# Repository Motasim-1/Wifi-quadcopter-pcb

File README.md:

# WiFi-Controlled Quadcopter PCB Using ESP32

Custom PCB design for a WiFi-controlled quadcopter based on the ESP32 microcontroller. The board was designed in KiCad, assembled using solder paste and a reflow oven, and tested with four motor outputs controlled through a mobile app.

## Project overview

The goal of this project was to design a compact quadcopter control PCB that integrates the main electronics on a single board and reduces external wiring.

## Key features

- ESP32-based control board with built-in WiFi capability
- Custom quadcopter-shaped PCB designed in KiCad
- Four motor-control outputs using MOSFET driver stages
- USB interface for programming/debugging
- SMD assembly using solder paste and reflow oven
- Power verification and short-circuit testing after assembly
- Functional motor testing using mobile-app WiFi control

## Hardware design

The KiCad project is located in:

```text
hardware/kicad/
```

Included schematic sheets:

```text
my_drone.kicad_sch
mcu.kicad_sch
motor.kicad_sch
power.kicad_sch
usb.kicad_sch
imu.kicad_sch
```

The PCB layout file is:

```text
my_drone.kicad_pcb
```

## Figures

### KiCad 3D view

### Assembled PCB

### Motor test setup

## Tools and technologies

- KiCad
- ESP32
- PCB design
- SMD soldering
- Reflow soldering
- MOSFET motor switching
- WiFi-based control
- Hardware testing and troubleshooting

## Firmware note

The original motor-control setup was tested using an existing mobile-control framework. This repository focuses on the custom PCB hardware design, assembly and validation. 
## Repository structure

```text
wifi-controlled-quadcopter-pcb/
├── README.md
├── .gitignore
├── hardware/
│   └── kicad/
├── figures/
## Documentation

- [View complete schematic (PDF)](docs/quadcopter_schematic.pdf)

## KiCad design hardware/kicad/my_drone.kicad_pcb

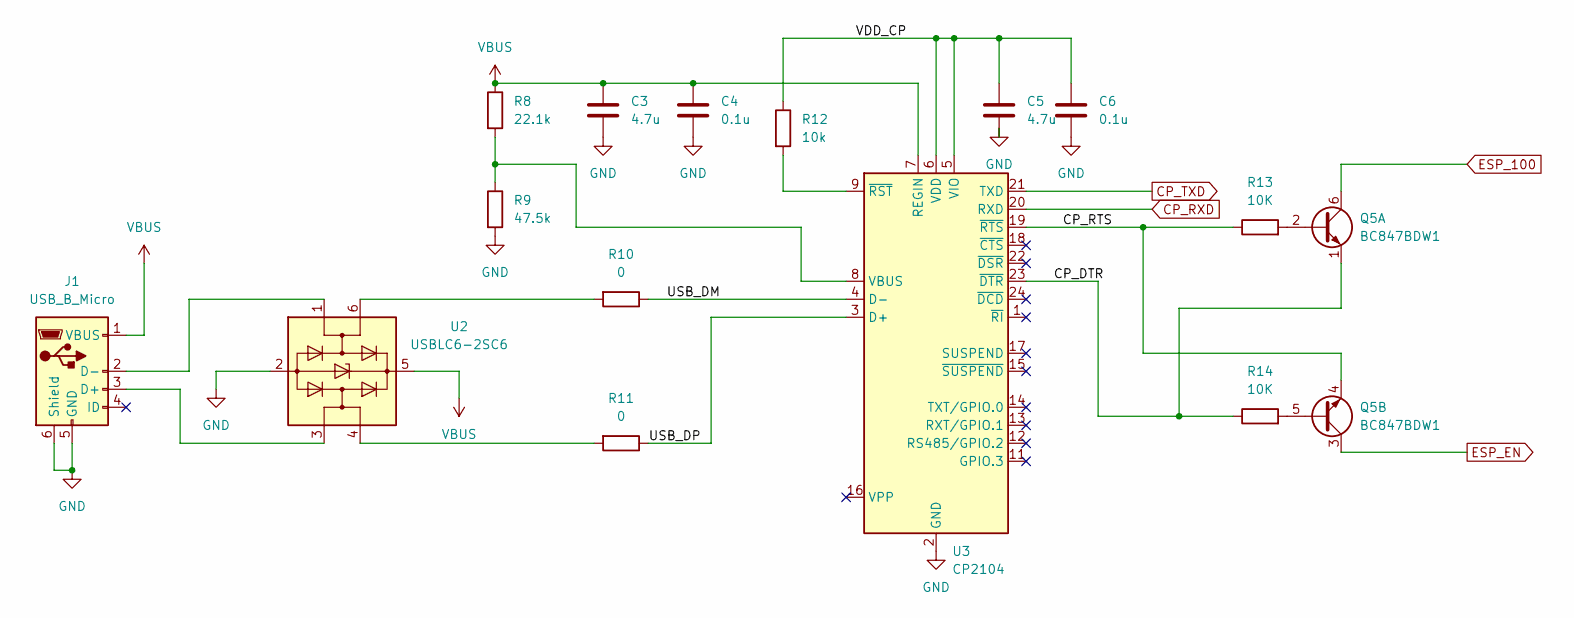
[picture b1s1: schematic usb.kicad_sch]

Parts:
C3, C5: 4.7u; C_0603_1608Metric
C4, C6: 0.1u; C_0603_1608Metric
J1: USB_B_Micro; USB_Micro
Q5: BC847BDW1; SOT-363_SC-70-6
R8: 22.1k; R_0603_1608Metric
R9: 47.5k; R_0603_1608Metric
R10, R11: 0; R_0603_1608Metric
R12: 10k; R_0603_1608Metric
R13, R14: 10K; R_0603_1608Metric
U2: USBLC6-2SC6; SOT-23-6; Digi-Key 497-5235-1-ND
U3: CP2104; QFN-24-1EP_4x4mm_P0.5mm_EP2.6x2.6mm; Digi-Key 336-4146-1-ND

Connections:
/*USB/CP_DTR: Q5.1 (E1), R14.1, U3.23 (~DTR)
/*USB/CP_RTS: Q5.4 (E2), R13.1, U3.19 (~RTS)
/*USB/USB_DM: R10.1, U3.4 (D-)
/*USB/USB_DP: R11.1, U3.3 (D+)
/*USB/VDD_CP: C5.1, C6.1, R12.1, U3.5 (VIO), U3.6 (VDD)
CP_RXD: U3.20 (RXD); also elsewhere on the board
CP_TXD: U3.21 (TXD); also elsewhere on the board
ESP_100: Q5.6 (C1); also elsewhere on the board
ESP_EN: Q5.3 (C2); also elsewhere on the board
GND: C3.2, C4.2, C5.2, C6.2, J1.5 (GND), J1.6 (Shield), R9.2, U2.2 (GND), U3.2 (GND), U3.25 (GND); also elsewhere on the board
unnamed: J1.3 (D+), U2.3 (I/O2)
unnamed: J1.2 (D-), U2.1 (I/O1)
unnamed: Q5.2 (B1), R13.2
unnamed: Q5.5 (B2), R14.2
unnamed: R10.2, U2.6 (I/O1)
unnamed: R11.2, U2.4 (I/O2)
unnamed: R8.2, R9.1, U3.8 (VBUS)
unnamed: R12.2, U3.9 (~RST)
VBUS: C3.1, C4.1, J1.1 (VBUS), R8.1, U2.5 (VBUS), U3.7 (REGIN); also elsewhere on the board

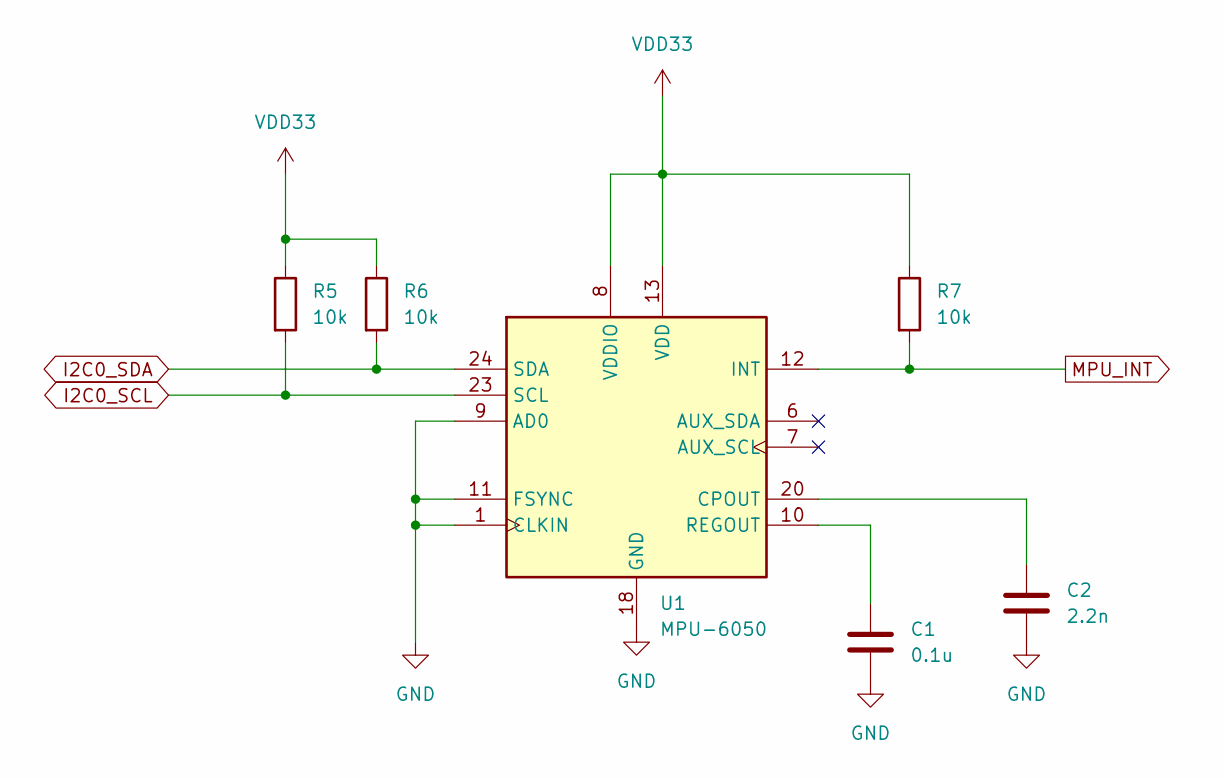
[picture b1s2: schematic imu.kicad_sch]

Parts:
C1: 0.1u; C_0603_1608Metric
C2: 2.2n; C_0603_1608Metric
R5, R6, R7: 10k; R_0603_1608Metric
U1: MPU-6050; InvenSense_QFN-24_4x4mm_P0.5mm

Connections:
GND: C1.2, C2.2, U1.1 (CLKIN), U1.9 (AD0), U1.11 (FSYNC), U1.18 (GND); also elsewhere on the board
I2C0_SCL: R5.2, U1.23 (SCL); also elsewhere on the board
I2C0_SDA: R6.2, U1.24 (SDA); also elsewhere on the board
MPU_INT: R7.2, U1.12 (INT); also elsewhere on the board
unnamed: C2.1, U1.20 (CPOUT)
unnamed: C1.1, U1.10 (REGOUT)
VDD33: R5.1, R6.1, R7.1, U1.8 (VDDIO), U1.13 (VDD); also elsewhere on the board

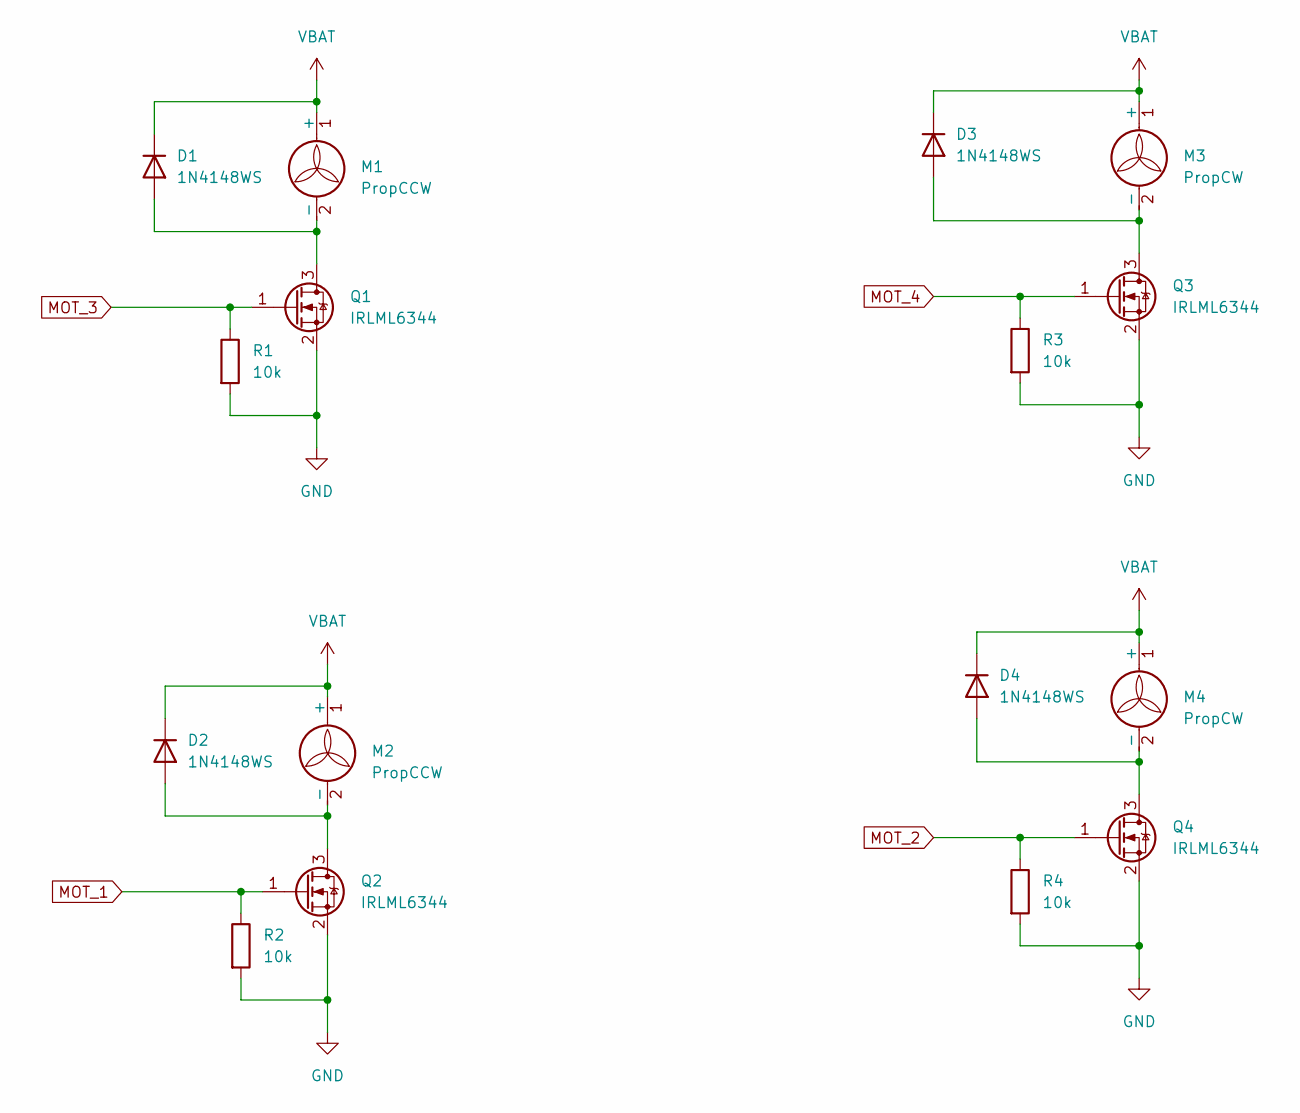
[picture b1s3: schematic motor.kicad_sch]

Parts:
D1, D2, D3, D4: 1N4148WS; D_SOD-323
M1, M2: PropCCW; PinHeader_1x02_P2.54mm_Vertical
M3, M4: PropCW; PinHeader_1x02_P2.54mm_Vertical
Q1, Q2, Q3, Q4: IRLML6344; SOT-23; Digi-Key IRLML6344TRPBFCT-ND
R1, R2, R3, R4: 10k; R_0603_1608Metric

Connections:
GND: Q1.2 (S), Q2.2 (S), Q3.2 (S), Q4.2 (S), R1.2, R2.2, R3.2, R4.2; also elsewhere on the board
MOT_1: Q2.1 (G), R2.1; also elsewhere on the board
MOT_2: Q4.1 (G), R4.1; also elsewhere on the board
MOT_3: Q1.1 (G), R1.1; also elsewhere on the board
MOT_4: Q3.1 (G), R3.1; also elsewhere on the board
unnamed: D1.2 (A), M1.2 (-), Q1.3 (D)
unnamed: D2.2 (A), M2.2 (-), Q2.3 (D)
unnamed: D3.2 (A), M3.2 (-), Q3.3 (D)
unnamed: D4.2 (A), M4.2 (-), Q4.3 (D)
VBAT: D1.1 (K), D2.1 (K), D3.1 (K), D4.1 (K), M1.1 (+), M2.1 (+), M3.1 (+), M4.1 (+); also elsewhere on the board

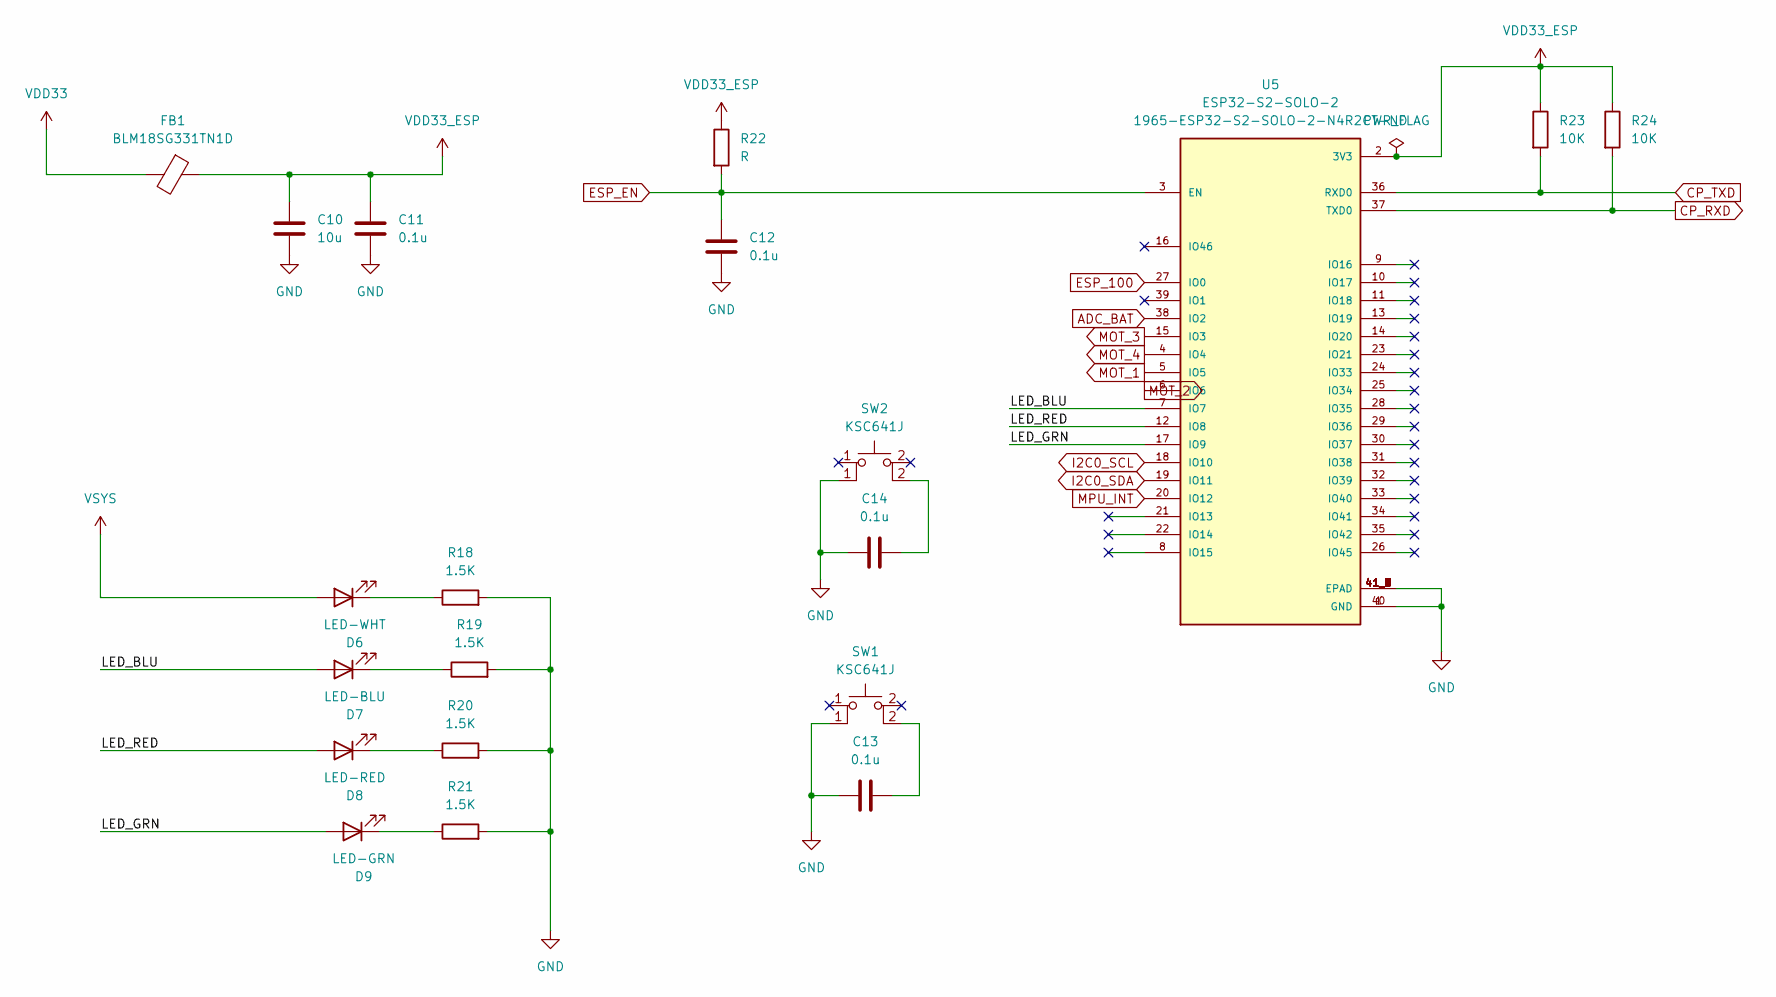
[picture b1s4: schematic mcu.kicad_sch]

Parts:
C10: 10u; C_0603_1608Metric
C11, C12, C13, C14: 0.1u; C_0603_1608Metric
D6: LED-WHT; LED_0603_1608Metric
D7: LED-BLU; LED_0603_1608Metric
D8: LED-RED; LED_0603_1608Metric
D9: LED-GRN; LED_0603_1608Metric
FB1: BLM18SG331TN1D; R_0603_1608Metric; Digi-Key 490-3997-1-ND
R18, R19, R20, R21: 1.5K; R_0603_1608Metric
R22: R; R_0603_1608Metric
R23, R24: 10K; R_0603_1608Metric
SW1, SW2: KSC641J; SW_Push_1P1T_NO_CK_KSC6xxJ; Digi-Key 401-1788-1-ND
U5: ESP32-S2-SOLO-2; Digi-Key 1965-ESP32-S2-SOLO-2-N4R2CT-ND

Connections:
/MCU/LED_BLU: D7.2 (A), U5.7 (IO7)
/MCU/LED_GRN: D9.2 (A), U5.17 (IO9)
/MCU/LED_RED: D8.2 (A), U5.12 (IO8)
ADC_BAT: U5.38 (IO2); also elsewhere on the board
CP_RXD: R24.2, U5.37 (TXD0); also elsewhere on the board
CP_TXD: R23.2, U5.36 (RXD0); also elsewhere on the board
ESP_100: U5.27 (IO0); also elsewhere on the board
ESP_EN: C12.1, R22.2, U5.3 (EN); also elsewhere on the board
GND: C10.2, C11.2, C12.2, C13.1, C14.1, R18.2, R19.2, R20.2, R21.2, SW1.1 (2), SW2.1 (2), U5.1 (GND), U5.40 (GND), U5.41_1 (EPAD), U5.41_2 (EPAD), U5.41_3 (EPAD), U5.41_4 (EPAD), U5.41_5 (EPAD), U5.41_6 (EPAD), U5.41_7 (EPAD), U5.41_8 (EPAD), U5.41_9 (EPAD); also elsewhere on the board
I2C0_SCL: U5.18 (IO10); also elsewhere on the board
I2C0_SDA: U5.19 (IO11); also elsewhere on the board
MOT_1: U5.5 (IO5); also elsewhere on the board
MOT_2: U5.6 (IO6); also elsewhere on the board
MOT_3: U5.15 (IO3); also elsewhere on the board
MOT_4: U5.4 (IO4); also elsewhere on the board
MPU_INT: U5.20 (IO12); also elsewhere on the board
unnamed: D6.1 (K), R18.1
unnamed: D7.1 (K), R19.1
unnamed: D8.1 (K), R20.1
unnamed: D9.1 (K), R21.1
unnamed: C13.2, SW1.2 (K)
unnamed: C14.2, SW2.2 (K)
VDD33: FB1.2; also elsewhere on the board
VDD33_ESP: C10.1, C11.1, FB1.1, R22.1, R23.1, R24.1, U5.2 (3V3)
VSYS: D6.2 (A); also elsewhere on the board

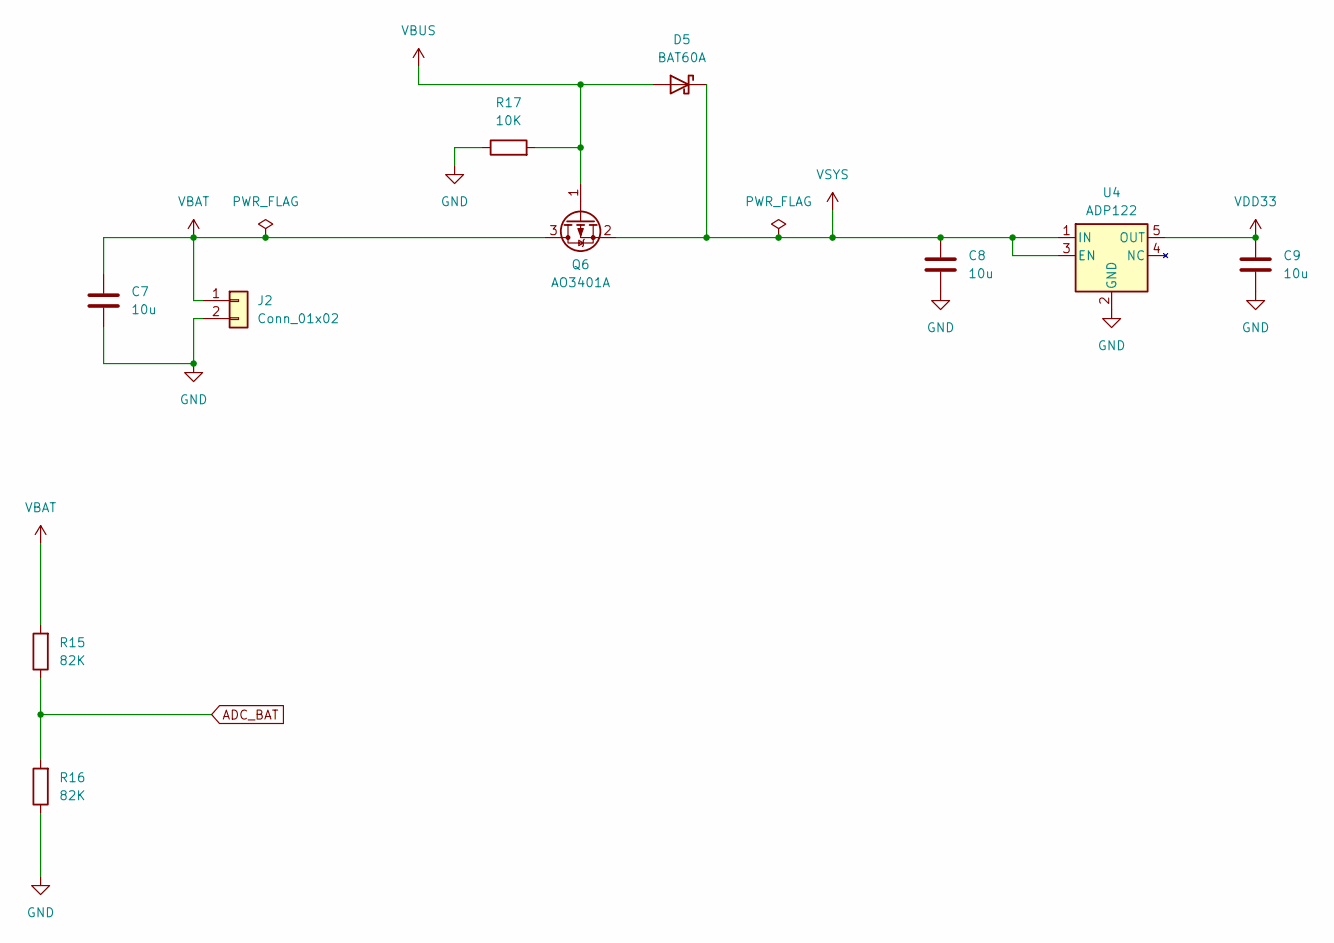
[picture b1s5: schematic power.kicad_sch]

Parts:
C7, C8, C9: 10u; C_0603_1608Metric
D5: BAT60A; D_SOD-323
J2: Conn_01x02; PinHeader_1x02_P2.00mm_Horizontal
Q6: AO3401A; SOT-23
R15, R16: 82K; R_0603_1608Metric
R17: 10K; R_0603_1608Metric
U4: ADP122; SOT-23-5; Digi-Key 505-ADP122AUJZ-3.3-R7CT-ND

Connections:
ADC_BAT: R15.1, R16.2; also elsewhere on the board
GND: C7.2, C8.2, C9.2, J2.2, R16.1, R17.1, U4.2 (GND); also elsewhere on the board
VBAT: C7.1, J2.1, Q6.3 (D), R15.2; also elsewhere on the board
VBUS: D5.2 (A), Q6.1 (G), R17.2; also elsewhere on the board
VDD33: C9.1, U4.5 (OUT); also elsewhere on the board
VSYS: C8.1, D5.1 (K), Q6.2 (S), U4.1 (IN), U4.3 (EN); also elsewhere on the board

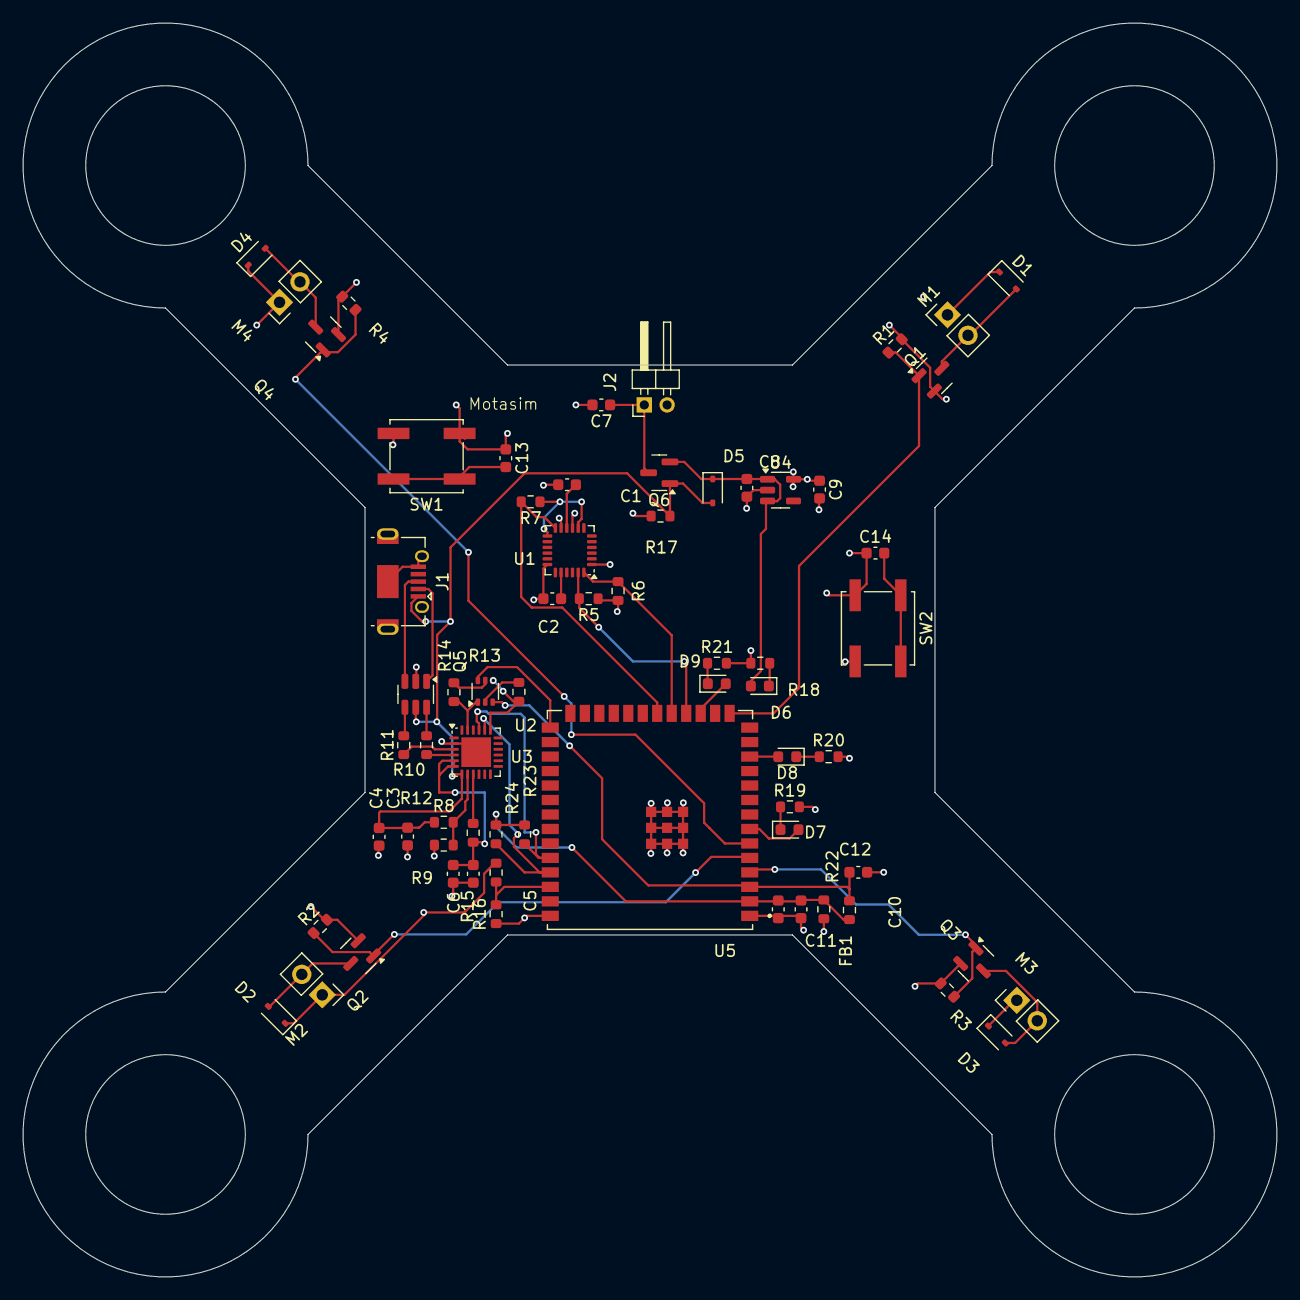
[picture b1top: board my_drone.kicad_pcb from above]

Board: 4 copper layers, 110.0 x 110.0 mm, 67 parts (0 on the bottom side), 46 nets.

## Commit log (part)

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2026-06-11 drone files
